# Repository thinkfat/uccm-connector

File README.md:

uccm-connector
==============

Connector board for UCCM GPSDO modules

This repository contains a KiCAD 5 project with a connector board for UCCM GPSDO boards.

Schematic
---------

The *doc* folder contains the schematic as PDF

Fabrication
-----------

The *gerber* folder contains Gerber plots and drill files. You can just ZIP this folder and upload it e.g. to JLCPCB to have the boards made.

BOM
---

Many of the passive parts are just generic beach sand stuff. If you look into the *bom* folder, there's a 
file _ibom.html_ that, if you open it in a browser, will give you an interactive part list that can guide you
with part ordering and assembly.

However, there's a few components that must match the footprint or are otherwise hard to find:

- DC jack: Lumberg NEB21R
- FPC socket: Molex 54132-5033
- FPC jumper cable: Molex 15166-0537
- Switching regulator: TI LMR14030SDDAR
- Storage coil: Coilcraft XAL5030-222MEC
- Flyback diode: Diodes B330BE-13
- Electrolytic caps: Panasonic EEE-FT1V470AR should fit
- Switcher input caps: TDK C3216X5R1H685K160AB
- Trimpot: Bourns 3313J-1-503E
- RS232 line converter: TI MAX3232ECDR
- DC input choke: Murata LQM31PN1R0M00L
- Reverse polarity protection: Diodes ES2BA-13-F
- LDO: APE8865N-33-HF-3

  this part is not really critical, just make sure you order a matching pin-out and take care of the dimensioning of the input and output caps.
  In fact even for this particular part you can deviate from the BOM and use 1µF MLCCs in 0805 size, they tend to be cheaper than the 4.7µF that
  are in the schematic.

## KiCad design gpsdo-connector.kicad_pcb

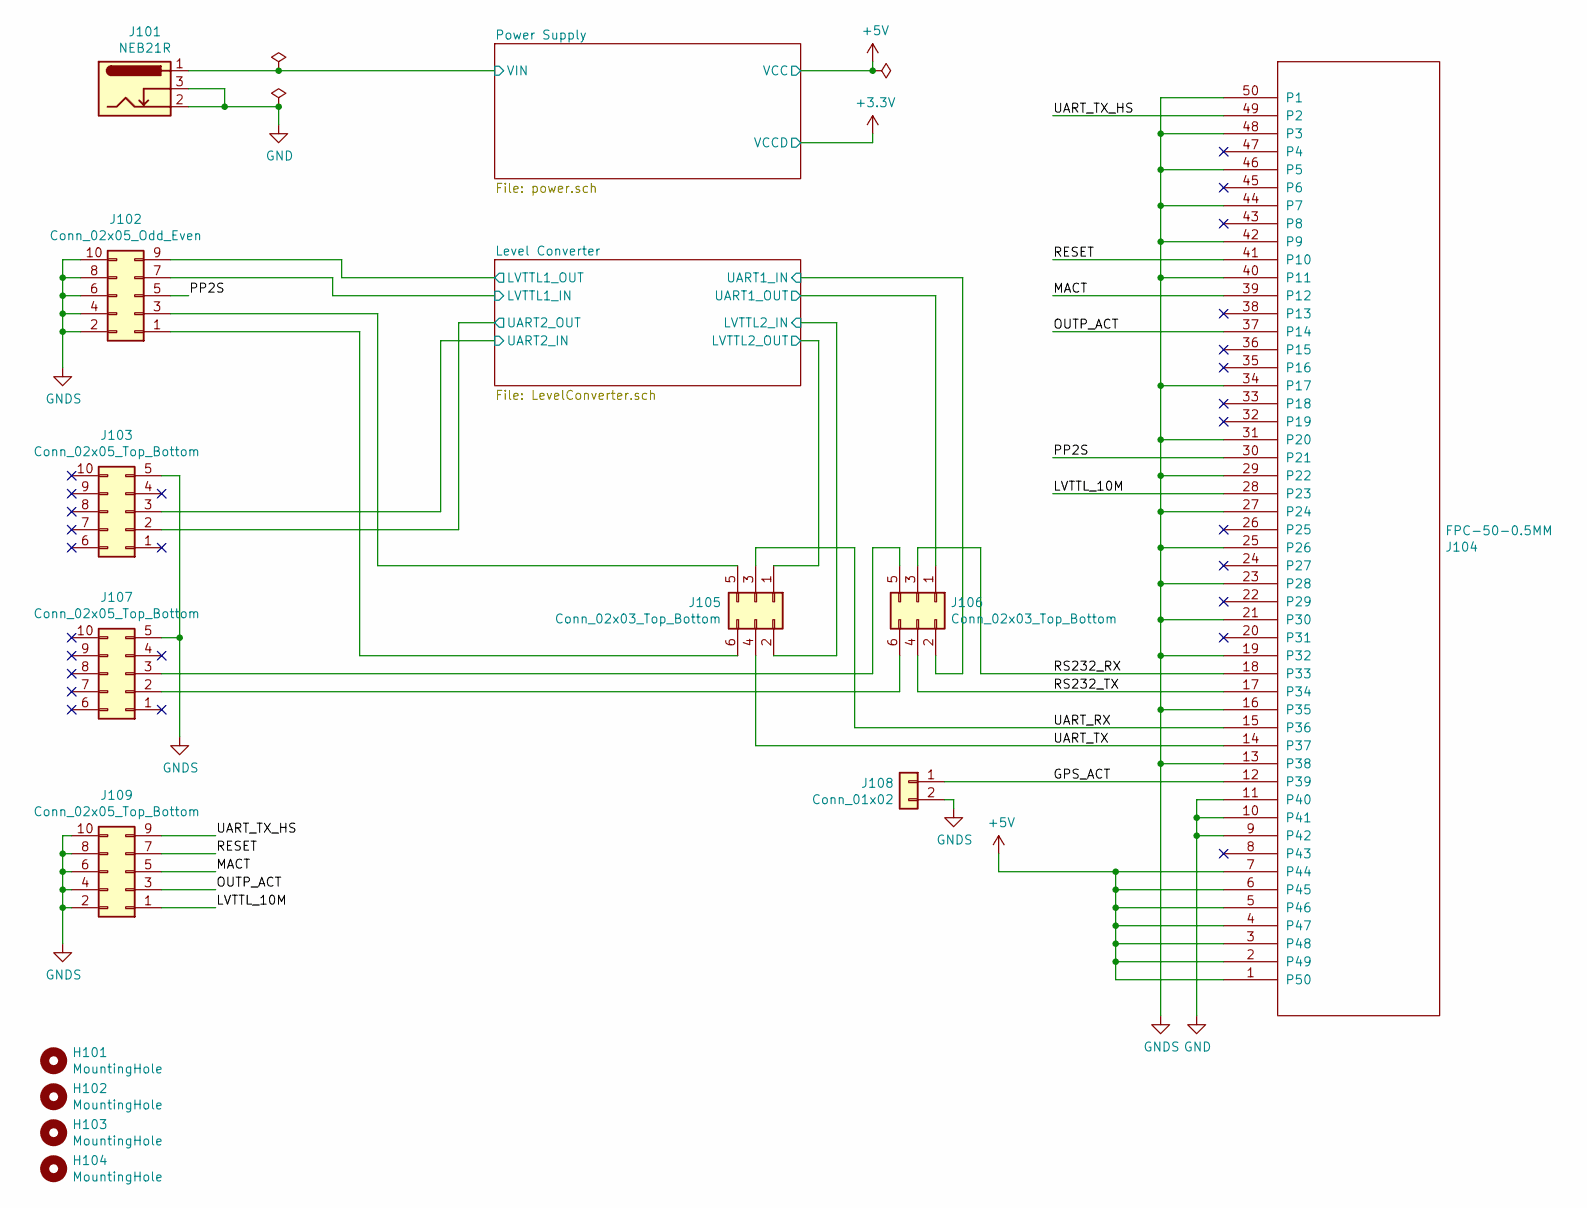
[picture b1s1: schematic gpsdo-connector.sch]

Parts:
H101, H102, H103, H104: MountingHole; MountingHole_3.2mm_M3_DIN965
J101: NEB21R
J102: Conn_02x05_Odd_Even; IDC-Header_2x05_P2.54mm_Vertical
J103, J107: Conn_02x05_Top_Bottom; IDC-Header_2x05_P2.54mm_Vertical
J104: FPC-50-0.5MM; Molex_54132-5033_1x50-1MP_P0.5mm_Horizontal
J105, J106: Conn_02x03_Top_Bottom; PinHeader_2x03_P2.54mm_Vertical
J108: Conn_01x02; PinHeader_1x02_P2.54mm_Vertical
J109: Conn_02x05_Top_Bottom; PinHeader_2x05_P2.54mm_Vertical

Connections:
+5V: J104.1 (P50), J104.2 (P49), J104.3 (P48), J104.4 (P47), J104.5 (P46), J104.6 (P45), J104.7 (P44); also elsewhere on the board
/GPS_ACT: J104.12 (P39), J108.1
/LVTTL_10M: J104.28 (P23), J109.1
/Level Converter/LVTTL1_IN: J102.7; also elsewhere on the board
/Level Converter/LVTTL1_OUT: J102.9; also elsewhere on the board
/Level Converter/LVTTL2_IN: J105.2; also elsewhere on the board
/Level Converter/LVTTL2_OUT: J105.1; also elsewhere on the board
/Level Converter/UART1_IN: J106.2; also elsewhere on the board
/Level Converter/UART1_OUT: J106.1; also elsewhere on the board
/Level Converter/UART2_IN: J103.3; also elsewhere on the board
/Level Converter/UART2_OUT: J103.2; also elsewhere on the board
/MACT: J104.39 (P12), J109.5
/OUTP_ACT: J104.37 (P14), J109.3
/PP2S: J102.5, J104.30 (P21)
/Power Supply/VIN: J101.1; also elsewhere on the board
/RESET: J104.41 (P10), J109.7
/RS232_RX: J104.18 (P33), J106.3
/RS232_TX: J104.17 (P34), J106.4
/UART_RX: J104.15 (P36), J105.3
/UART_TX: J104.14 (P37), J105.4
/UART_TX_HS: J104.49 (P2), J109.9
GND: J101.2, J101.3, J104.9 (P42), J104.10 (P41), J104.11 (P40); also elsewhere on the board
GNDS: J102.2, J102.4, J102.6, J102.8, J102.10, J103.5, J104.13 (P38), J104.16 (P35), J104.19 (P32), J104.21 (P30), J104.23 (P28), J104.25 (P26), J104.27 (P24), J104.29 (P22), J104.31 (P20), J104.34 (P17), J104.40 (P11), J104.42 (P9), J104.44 (P7), J104.46 (P5), J104.48 (P3), J104.50 (P1), J107.5, J108.2, J109.2, J109.4, J109.6, J109.8, J109.10; also elsewhere on the board
unnamed: J102.1, J105.6
unnamed: J102.3, J105.5
unnamed: J106.5, J107.3
unnamed: J106.6, J107.2

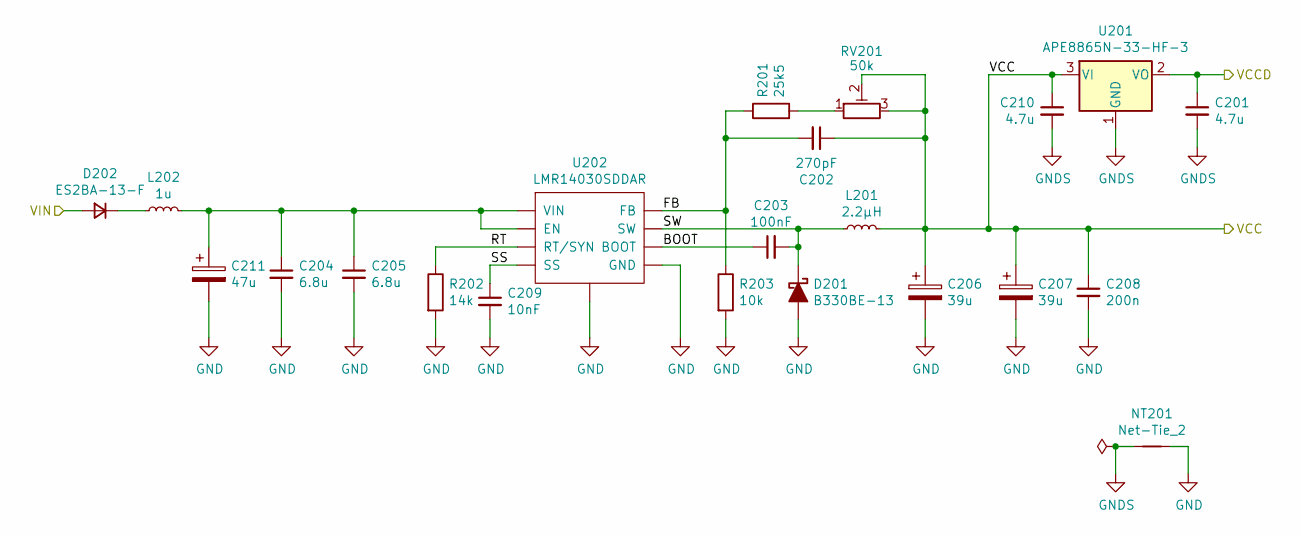
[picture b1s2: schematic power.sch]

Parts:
C201, C210: 4.7u; C_0805_2012Metric
C202: 270pF; C_0805_2012Metric
C203: 100nF; C_0805_2012Metric
C204, C205: 6.8u; C_1206_3216Metric
C206, C207: 39u; CP_Elec_5x5.9
C208: 200n; C_0805_2012Metric
C209: 10nF; C_0805_2012Metric
C211: 47u; CP_Elec_5x5.9
D201: B330BE-13; D_SMB
D202: ES2BA-13-F; D_SMA
L201: 2.2µH; L_Coilcraft_XAL5030
L202: 1u; L_1206_3216Metric
NT201: Net-Tie_2; NetTie-2_SMD_Pad2.0mm
R201: 25k5; R_0805_2012Metric
R202: 14k; R_0805_2012Metric_Pad1.15x1.40mm_HandSolder
R203: 10k; R_0805_2012Metric_Pad1.15x1.40mm_HandSolder
RV201: 50k; Trimpot_Bourns_3313J-1
U201: APE8865N-33-HF-3; SOT-23
U202: LMR14030SDDAR; TI_SO-PowerPAD-8

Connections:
+3V3: C201.1, U201.2 (VO); also elsewhere on the board
+5V: C202.1, C206.1, C207.1, C208.1, C210.1, L201.2, RV201.2, RV201.3, U201.3 (VI); also elsewhere on the board
/Power Supply/BOOT: C203.1, U202.1 (BOOT)
/Power Supply/FB: C202.2, R201.1, R203.1, U202.5 (FB)
/Power Supply/RT: R202.1, U202.4 (RT/SYN)
/Power Supply/SS: C209.1, U202.6 (SS)
/Power Supply/SW: C203.2, D201.1 (K), L201.1, U202.8 (SW)
/Power Supply/VIN: D202.2 (A); also elsewhere on the board
GND: C204.2, C205.2, C206.2, C207.2, C208.2, C209.2, C211.2, D201.2 (A), NT201.2, R202.2, R203.2, U202.7 (GND), U202.9; also elsewhere on the board
GNDS: C201.2, C210.2, NT201.1, U201.1 (GND); also elsewhere on the board
unnamed: C204.1, C205.1, C211.1, L202.2, U202.2 (VIN), U202.3 (EN)
unnamed: D202.1 (K), L202.1
unnamed: R201.2, RV201.1

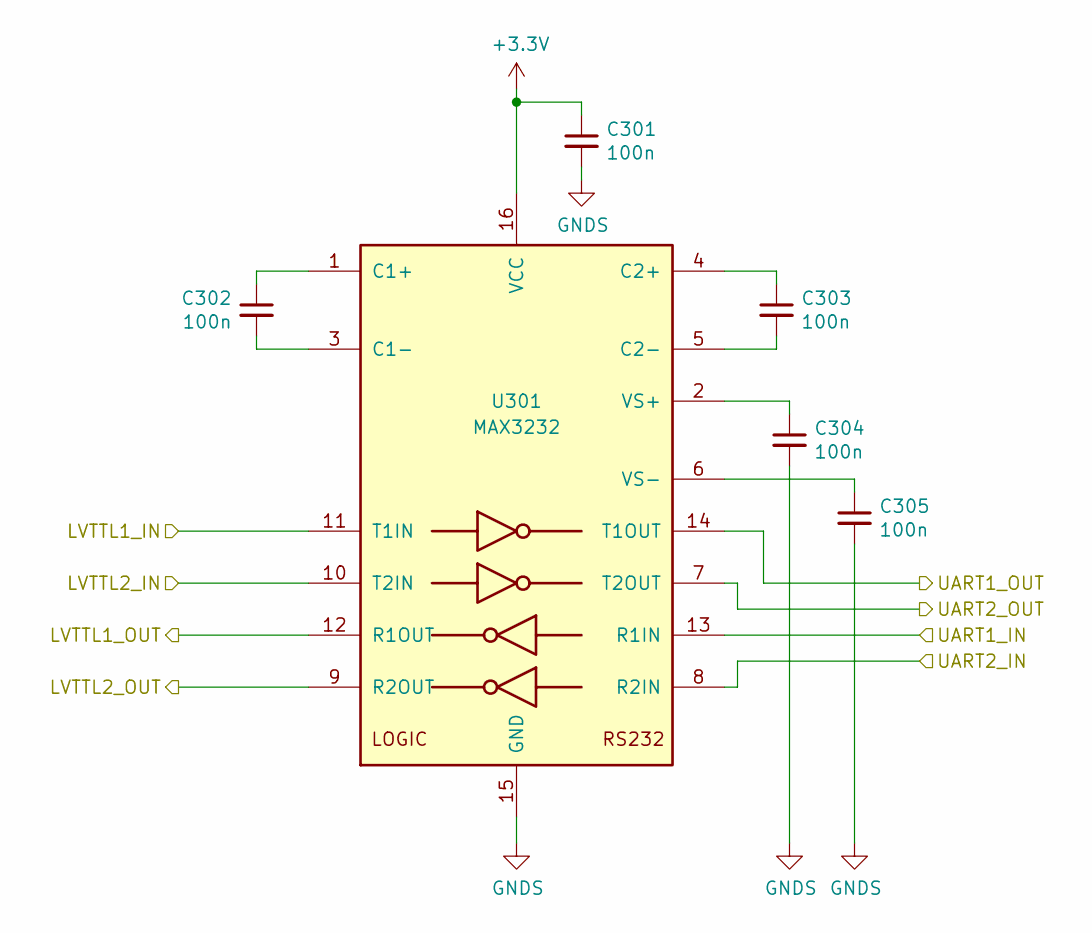
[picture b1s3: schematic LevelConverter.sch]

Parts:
C301, C302, C303, C304, C305: 100n; C_0805_2012Metric
U301: MAX3232; SOIC-16_3.9x9.9mm_P1.27mm

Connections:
+3V3: C301.1, U301.16 (VCC); also elsewhere on the board
/Level Converter/LVTTL1_IN: U301.11 (T1IN); also elsewhere on the board
/Level Converter/LVTTL1_OUT: U301.12 (R1OUT); also elsewhere on the board
/Level Converter/LVTTL2_IN: U301.10 (T2IN); also elsewhere on the board
/Level Converter/LVTTL2_OUT: U301.9 (R2OUT); also elsewhere on the board
/Level Converter/UART1_IN: U301.13 (R1IN); also elsewhere on the board
/Level Converter/UART1_OUT: U301.14 (T1OUT); also elsewhere on the board
/Level Converter/UART2_IN: U301.8 (R2IN); also elsewhere on the board
/Level Converter/UART2_OUT: U301.7 (T2OUT); also elsewhere on the board
GNDS: C301.2, C304.2, C305.2, U301.15 (GND); also elsewhere on the board
unnamed: C302.1, U301.1 (C1+)
unnamed: C302.2, U301.3 (C1-)
unnamed: C303.1, U301.4 (C2+)
unnamed: C303.2, U301.5 (C2-)
unnamed: C304.1, U301.2 (VS+)
unnamed: C305.1, U301.6 (VS-)

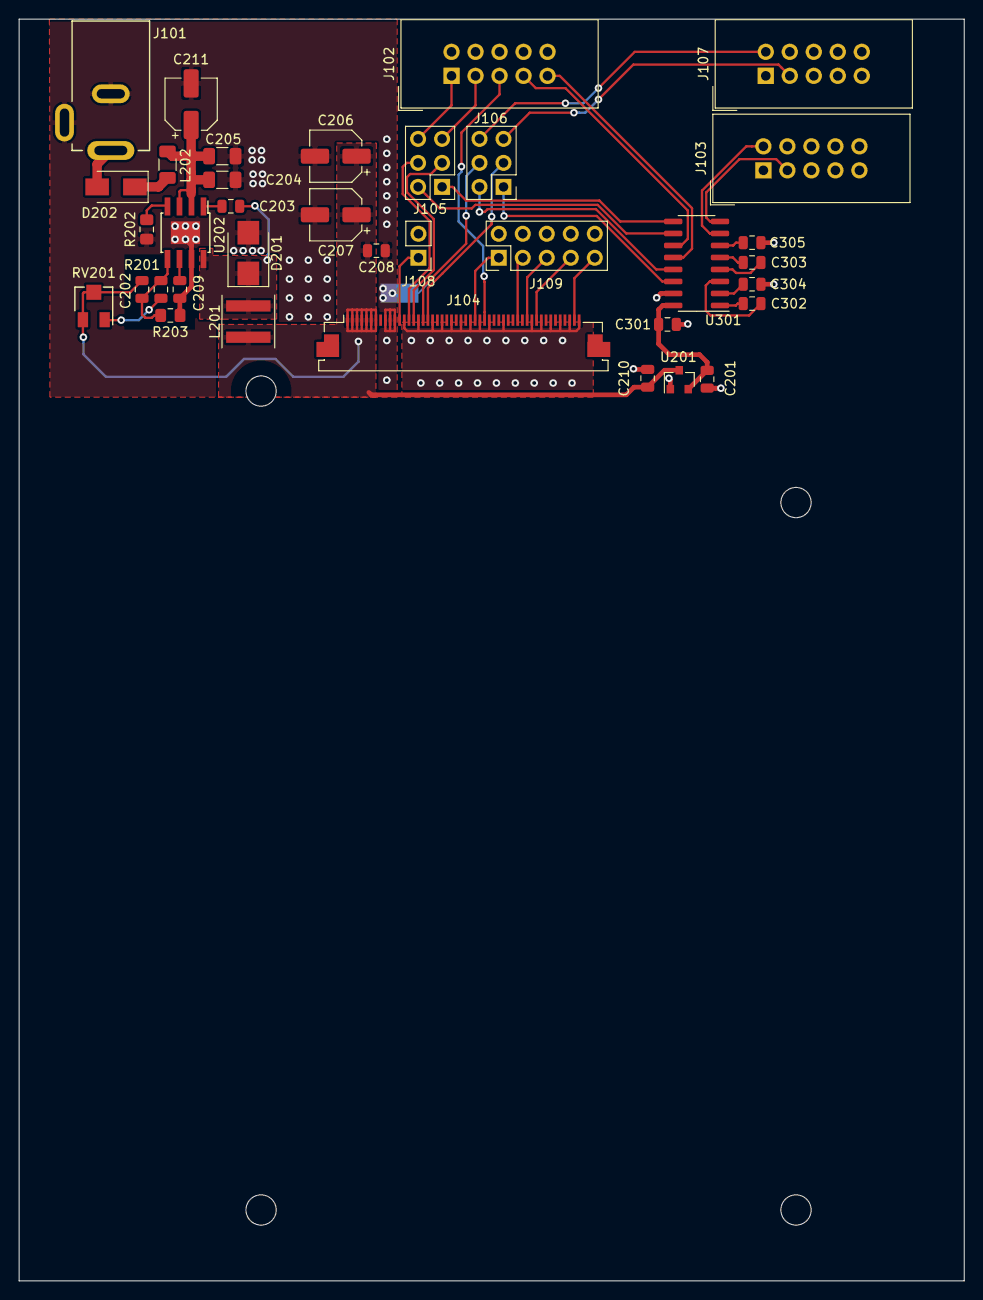
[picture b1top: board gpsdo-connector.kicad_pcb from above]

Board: 2 copper layers, 100.0 x 133.5 mm, 41 parts (1 on the bottom side), 42 nets.
